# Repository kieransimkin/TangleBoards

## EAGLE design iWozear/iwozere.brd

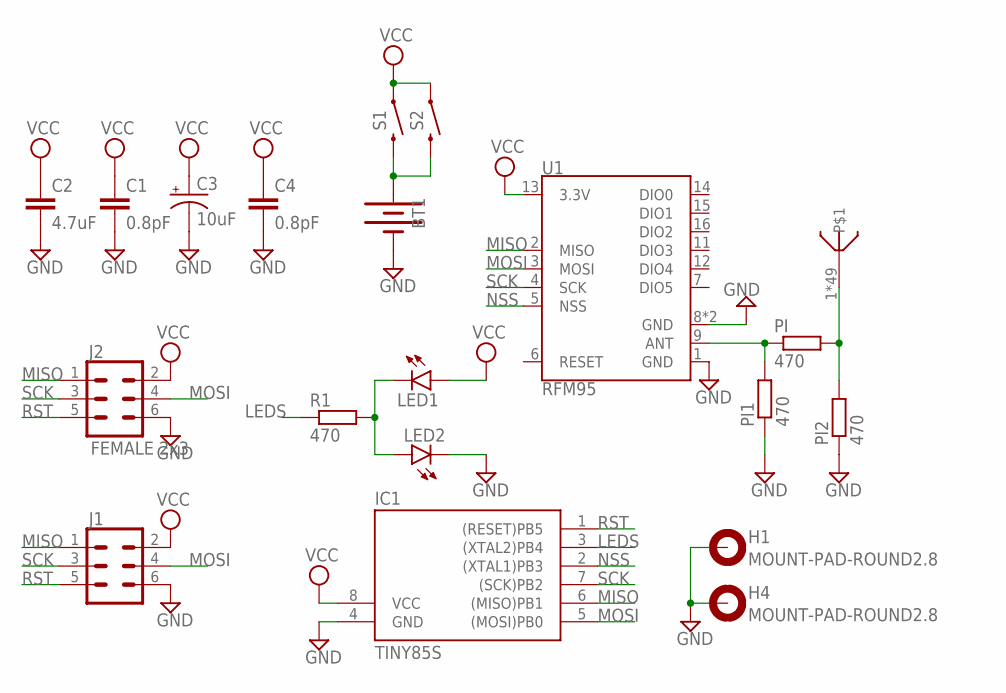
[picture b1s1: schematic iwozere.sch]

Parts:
BT1: BATTERY-20MM_SMD; BATTCON_20MM
C1, C4: 0.8pF; 0402
C2: 4.7uF; 1206
C3: 10uF; CPOL-RADIAL-2.5MM-5MM
H1, H4: MOUNT-PAD-ROUND2.8; 2,8-PAD
IC1: TINY85S; SOIC8
J1: CONN_03X2SMT; 2X3_SMT_POSTS
J2: FEMALE 2x3; 2X3
LED1, LED2: LEDCHIP-LED0603; CHIP-LED0603
PI, PI1, PI2: 470; R0603
R1: 470; R0603
S1: MOMENTARY-SWITCH-SPST-SMD-RIGHT-ANGLE; TACTILE_SWITCH_SMD_RIGHT_ANGLE
S2: MOMENTARY-SWITCH-SPST-PTH-RIGHT-ANGLE-KIT; TACTILE_SWITCH_PTH_RIGHT_ANGLE_KIT
U1: RFM95; RFM69HCW-XXXS2
U$1: 868MONOPOLEANTENNA; RESC3216X70N

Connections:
GND: BT1.2 (-), C1.2, C2.2, C3.2 (-), C4.2, H1.B2,8, H4.B2,8, IC1.4 (GND), J1.6, J2.6, LED2.C, PI1.1, PI2.1, U1.1 (GND), U1.8 (GND), U1.10 (GND)
LEDS: IC1.3 ((XTAL2)PB4), R1.1
MISO: IC1.6 ((MISO)PB1), J1.1, J2.1, U1.2 (MISO)
MOSI: IC1.5 ((MOSI)PB0), J1.4, J2.4, U1.3 (MOSI)
unnamed: BT1.1 (+), S1.2, S2.2
unnamed: PI.1, PI1.2, U1.9 (ANT)
unnamed: LED1.C, LED2.A, R1.2
unnamed: PI.2, PI2.2, U$1.1, U$1.P$1, U$1.P$2, U$1.P$3, U$1.P$4, U$1.P$5, U$1.P$6, U$1.P$7, U$1.P$8, U$1.P$9, U$1.P$10, U$1.P$11, U$1.P$12, U$1.P$13, U$1.P$14, U$1.P$15, U$1.P$16, U$1.P$17, U$1.P$18, U$1.P$19, U$1.P$20, U$1.P$21, U$1.P$22, U$1.P$23, U$1.P$24, U$1.P$25, U$1.P$26, U$1.P$27, U$1.P$28, U$1.P$29, U$1.P$30, U$1.P$31, U$1.P$32, U$1.P$33, U$1.P$34, U$1.P$35, U$1.P$36, U$1.P$37, U$1.P$38, U$1.P$39, U$1.P$40, U$1.P$41, U$1.P$42, U$1.P$43, U$1.P$44, U$1.P$45, U$1.P$46, U$1.P$47, U$1.P$48
NSS: IC1.2 ((XTAL1)PB3), U1.5 (NSS)
RST: IC1.1 ((RESET)PB5), J1.5, J2.5
SCK: IC1.7 ((SCK)PB2), J1.3, J2.3, U1.4 (SCK)
VCC: C1.1, C2.1, C3.1 (+), C4.1, IC1.8 (VCC), J1.2, J2.2, LED1.A, S1.1, S2.1, U1.13 (3.3V)

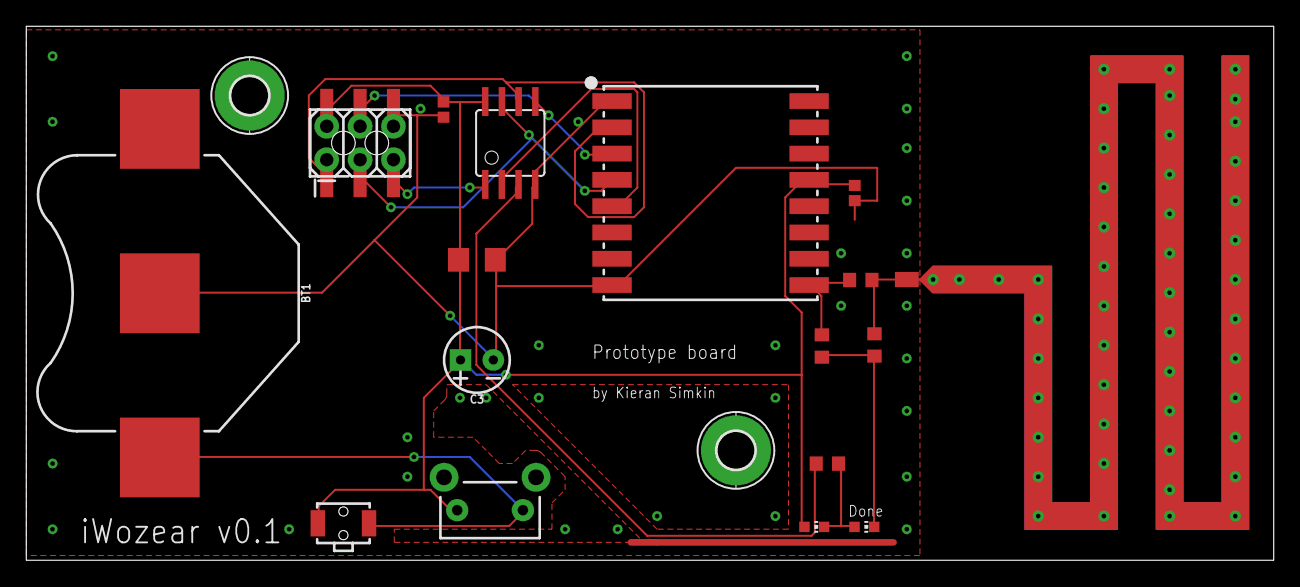
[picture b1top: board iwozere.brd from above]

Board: 2 copper layers, 94.9 x 40.6 mm, 20 parts (0 on the bottom side), 12 nets.

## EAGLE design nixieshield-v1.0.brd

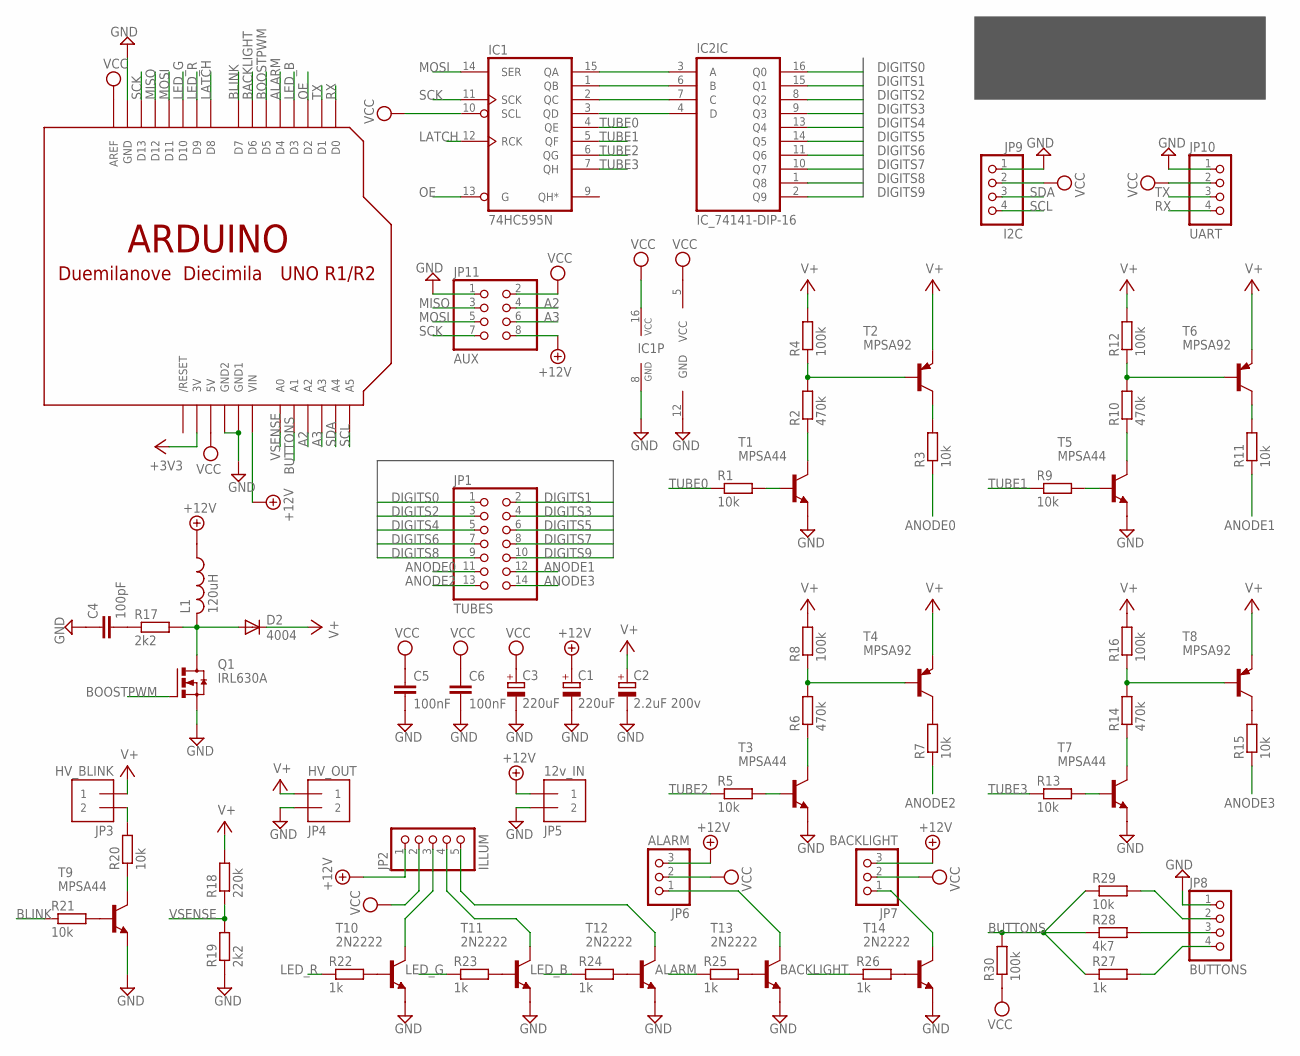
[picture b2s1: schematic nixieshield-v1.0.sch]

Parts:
C1, C3: 220uF; E1,8-4
C2: 2.2uF 200v; E1,8-4
C4: 100pF; C025-024X044
C5, C6: 100nF; C025-024X044
D2: 4004; D-7.5
IC1: 74HC595N; DIL16
IC2: IC_74141-DIP-16; DIL16
JP1: TUBES; 2X07
JP2: ILLUM; 1X05
JP3: HV_BLINK; 1X2-3.5MM
JP4: HV_OUT; 1X2-3.5MM
JP5: 12v_IN; 1X2-3.5MM
JP6: ALARM; 1X03
JP7: BACKLIGHT; 1X03
JP8: BUTTONS; 1X04
JP9: I2C; 1X04
JP10: UART; 1X04
JP11: AUX; 2X04
L1: 120uH; 0207/2V
Q1: IRL630A; TO220AV
R1, R3, R5, R7, R9, R11, R13, R15, R20, R21, R29: 10k; 0204/7
R2, R6, R10, R14: 470k; 0204/7
R4, R8, R12, R16, R30: 100k; 0204/7
R17, R19: 2k2; 0204/7
R18: 220k; 0204/7
R22, R23, R24, R25, R26, R27: 1k; 0204/7
R28: 4k7; 0204/7
T1, T3, T5, T7, T9: MPSA44; TO92-EBC
T2, T4, T6, T8: MPSA92; TO92-EBC
T10, T11, T12, T13, T14: 2N2222; TO92-EBC-OVAL
U$1: ARDUINOUNO; ARDUINO

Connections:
+3V3: U$1.3V
+12V: C1.+, JP2.1, JP5.1, JP6.3, JP7.3, JP11.8, L1.1, U$1.VIN
A2: JP11.4, U$1.A2
A3: JP11.6, U$1.A3
ALARM: R25.1, U$1.D4
ANODE0: JP1.11, R3.1
ANODE1: JP1.12, R11.1
ANODE2: JP1.13, R7.1
ANODE3: JP1.14, R15.1
BACKLIGHT: R26.1, U$1.D6
BLINK: R21.1, U$1.D7
BOOSTPWM: Q1.B (G), U$1.D5
BUTTONS: R27.1, R28.1, R29.1, R30.2, U$1.A1
DIGITS0: IC2.16 (Q0), JP1.1
DIGITS1: IC2.15 (Q1), JP1.2
DIGITS2: IC2.8 (Q2), JP1.3
DIGITS3: IC2.9 (Q3), JP1.4
DIGITS4: IC2.13 (Q4), JP1.5
DIGITS5: IC2.14 (Q5), JP1.6
DIGITS6: IC2.11 (Q6), JP1.7
DIGITS7: IC2.10 (Q7), JP1.8
DIGITS8: IC2.1 (Q8), JP1.9
DIGITS9: IC2.2 (Q9), JP1.10
GND: C1.-, C2.-, C3.-, C4.1, C5.2, C6.2, IC1.8 (GND), IC2.12 (GND), JP4.2, JP5.2, JP8.1, JP9.1, JP10.1, JP11.1, Q1.E (S), R19.1, T1.E, T3.E, T5.E, T7.E, T9.E, T10.E, T11.E, T12.E, T13.E, T14.E, U$1.GND, U$1.GND1, U$1.GND2
LATCH: IC1.12 (RCK), U$1.D8
LED_B: R24.1, U$1.D3
LED_G: R23.1, U$1.D10
LED_R: R22.1, U$1.D9
MISO: JP11.3, U$1.D12
MOSI: IC1.14 (SER), JP11.5, U$1.D11
unnamed: IC1.1 (QB), IC2.6 (B)
unnamed: IC1.2 (QC), IC2.7 (C)
unnamed: IC1.3 (QD), IC2.4 (D)
unnamed: IC1.15 (QA), IC2.3 (A)
unnamed: R2.1, T1.C
unnamed: R1.2, T1.B
unnamed: R3.2, T2.C
unnamed: R2.2, R4.1, T2.B
unnamed: R5.2, T3.B
unnamed: R7.2, T4.C
unnamed: R6.1, T3.C
unnamed: R6.2, R8.1, T4.B
unnamed: R9.2, T5.B
unnamed: R11.2, T6.C
unnamed: R10.1, T5.C
unnamed: R10.2, R12.1, T6.B
unnamed: R13.2, T7.B
unnamed: R15.2, T8.C
unnamed: R14.1, T7.C
unnamed: R14.2, R16.1, T8.B
unnamed: D2.A, L1.2, Q1.C (D), R17.2
unnamed: C4.2, R17.1
unnamed: R20.1, T9.C
unnamed: R21.2, T9.B
unnamed: R22.2, T10.B
unnamed: R23.2, T11.B
unnamed: R24.2, T12.B
unnamed: R25.2, T13.B
unnamed: JP2.3, T10.C
unnamed: JP2.4, T11.C
unnamed: JP2.5, T12.C
unnamed: JP3.2, R20.2
unnamed: JP6.1, T13.C
unnamed: R26.2, T14.B
unnamed: JP7.1, T14.C
unnamed: JP8.4, R27.2
unnamed: JP8.3, R28.2
unnamed: JP8.2, R29.2
OE: IC1.13 (G), U$1.D2
RX: JP10.4, U$1.D0
SCK: IC1.11 (SCK), JP11.7, U$1.D13
SCL: JP9.4, U$1.A5
SDA: JP9.3, U$1.A4
TUBE0: IC1.4 (QE), R1.1
TUBE1: IC1.5 (QF), R9.1
TUBE2: IC1.6 (QG), R5.1
TUBE3: IC1.7 (QH), R13.1
TX: JP10.3, U$1.D1
V+: C2.+, D2.C, JP3.1, JP4.1, R4.2, R8.2, R12.2, R16.2, R18.2, T2.E, T4.E, T6.E, T8.E
VCC: C3.+, C5.1, C6.1, IC1.10 (SCL), IC1.16 (VCC), IC2.5 (VCC), JP2.2, JP6.2, JP7.2, JP9.2, JP10.2, JP11.2, R30.1, U$1.5V, U$1.AREF
VSENSE: R18.1, R19.2, U$1.A0

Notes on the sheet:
Arduino Nixie Clock Shield
Kieran Simkin - http://slinq.com/
v1.0

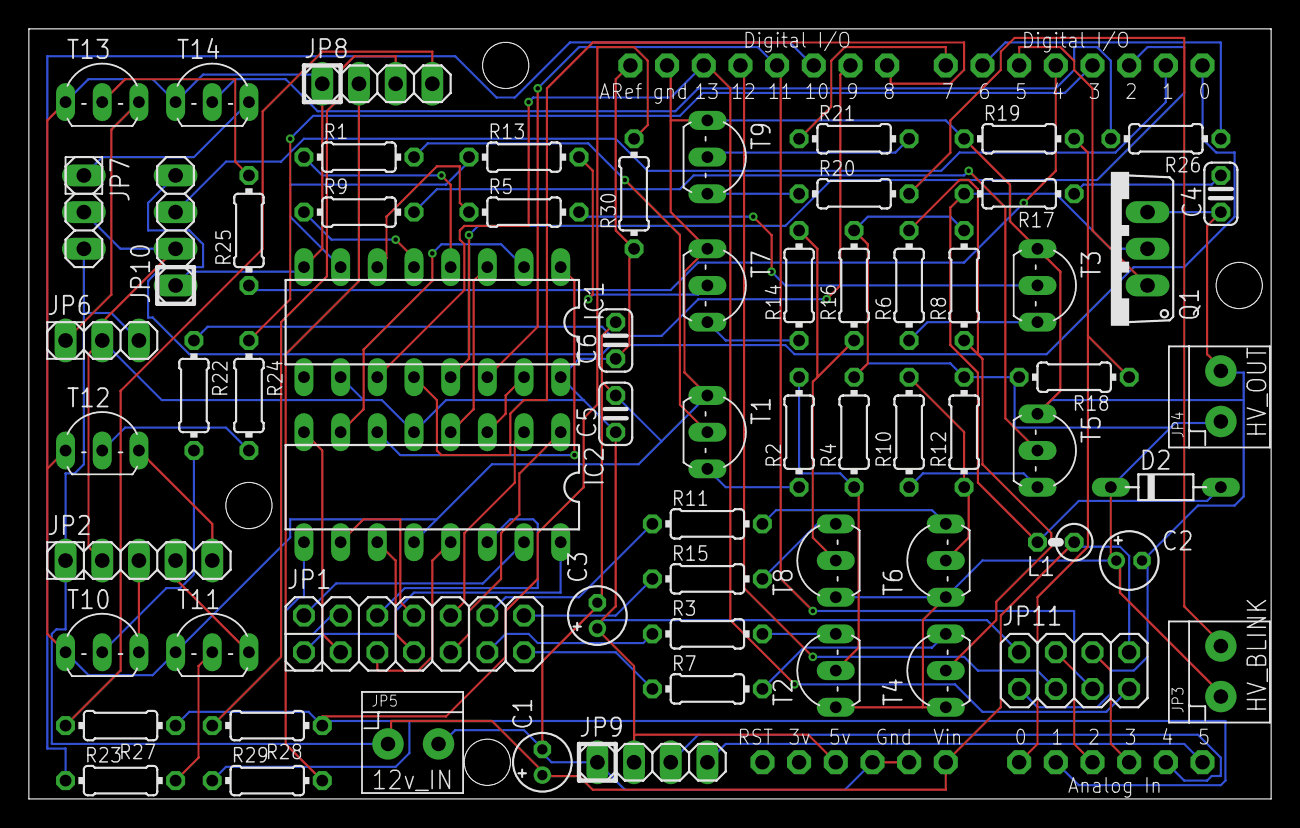
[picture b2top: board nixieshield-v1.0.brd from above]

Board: 2 copper layers, 86.0 x 53.3 mm, 67 parts (0 on the bottom side), 80 nets.

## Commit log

2016-06-02 First version of nixieshield
2022-08-05 Adding iWozear
2022-08-05 Adding schematic pngs

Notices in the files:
parts and their libraries:
SparkFun-Batteries: Licensing: Creative Commons ShareAlike 4.0 International - https://creativecommons.org/licenses/by-sa/4.0
